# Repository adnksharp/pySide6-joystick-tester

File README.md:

# Reading joysticks

Lectura de joysticks para revisar problemas de drift con arduino y pySide6.

## Requisitos

[FirmataExpress](https://mryslab.github.io/pymata4/firmata_express/#installation-instructions)

### Librerías de Python

- PySide6
- pymata4
- matlotlib

```bash
pip install -r requirements.txt
```

### Hardware usado

|  |  |
|----|----|

- Placa de Arduino MEGA 2560.
- Modulo de joystick para Arduino.

## Características
- Graficar la lectura de un joystick en `x`, `y`, dentro de un scatterplot.
- Mostrar los valores del joystick en lcdnumbers.

### En proceso

> [!TIP]
>
> - Lectura de varios joysticks a la vez.

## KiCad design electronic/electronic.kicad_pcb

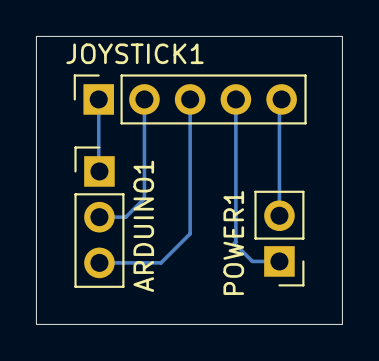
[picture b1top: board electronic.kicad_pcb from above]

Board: 2 copper layers, 17.0 x 16.0 mm, 3 parts (0 on the bottom side), 5 nets.

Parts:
ARDUINO1: Conn_01x03; PinHeader_1x03_P2.54mm_Vertical
JOYSTICK1: Conn_01x05; PinSocket_1x05_P2.54mm_Vertical
POWER1: Conn_01x02; PinHeader_1x02_P2.54mm_Vertical

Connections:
+5V: JOYSTICK1.4, POWER1.1
A0: ARDUINO1.3, JOYSTICK1.3
A1: ARDUINO1.2, JOYSTICK1.2
D2: ARDUINO1.1, JOYSTICK1.1
GNDREF: JOYSTICK1.5, POWER1.2

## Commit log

2024-12-09 chore: init.
2024-12-09 style: form defined.
2024-12-09 feat: scatter plot added.
2024-12-09 feat: arduino config defined.
2024-12-09 feat: display data.
2024-12-09 docs: create README.md
2024-12-10 chore: kidad electronic design added.
2024-12-10 docs: update README.md
